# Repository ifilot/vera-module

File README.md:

# VERA Module Fork

This repository is a fork of the VERA module, the Video Embedded Retro Adapter
developed for the Commander X16 computer. It contains the PCB designs, FPGA
source, firmware, programmer utilities, documentation, and manufacturing support
files for the module.

This fork keeps the original project history available while adding forked PCB
variants that can be reviewed, rendered, and published independently from the
upstream Commander X16-branded board files.

## What Changed In This Fork

- Added `pcb/fork-r0/` as the first forked board variant.
- Added `pcb/fork-r1/` as the current forked board variant.
- Removed/reworked branding that should not be reused outside the Commander X16
  project.
- Migrated the fork boards to modern KiCad project files.
- Added local symbol/cache fixes for migrated KiCad schematics so parts render
  and connect as intended.
- Added Docker-based placement-site generation for `fork-r0` and `fork-r1`.
- Added a GitHub Pages workflow that can publish the generated placement site.

The older upstream board revisions remain under `pcb/rev0/` through `pcb/rev4/`
for reference.

## Repository Layout

- `pcb/fork-r0/`: first forked PCB variant.
- `pcb/fork-r1/`: current forked PCB variant.
- `pcb/rev*/`: original/upstream board revisions.
- `fpga/`: VERA FPGA source and project files.
- `programmer/stm32/`: STM32 firmware for the programmer.
- `programmer/programmer_tool/`: host-side programmer tool.
- `doc/`: VERA documentation and datasheets.
- `deploy/`: scripts and configuration for generated placement and manufacturing
  outputs.

## Placement Website

Generate the placement website locally with:

```sh
./deploy/generate-placement-site.sh
```

The default build intentionally renders only the two fork boards:

- `pcb/fork-r0/fork-r0.kicad_pcb`
- `pcb/fork-r1/fork-r1.kicad_pcb`

The generated output is written to:

- `deploy/site/index.html`
- `deploy/site/fork-r0/index.html`
- `deploy/site/fork-r0/placements.csv`
- `deploy/site/fork-r1/index.html`
- `deploy/site/fork-r1/placements.csv`

The script prefers the Docker image `ghcr.io/inti-cmnb/kicad10_auto:latest`,
which contains KiCad, KiBot, and InteractiveHtmlBom. If Docker is unavailable, it
falls back to local KiBot/InteractiveHtmlBom tools, and finally to a limited
built-in preview generator.

## Manufacturing Files

Generate the complete local manufacturing package with:

```sh
./deploy/generate-manufacturing-files.sh
```

This generates Gerbers, Excellon drill files, zipped Gerber upload packages, and
the JLCPCB BOM/CPL files for only the fork boards:

- `manufacturing/gerbers/fork-r0/`
- `manufacturing/gerbers/fork-r0.zip`
- `manufacturing/gerbers/fork-r1/`
- `manufacturing/gerbers/fork-r1.zip`
- `manufacturing/jlcpcb/fork-r0/`
- `manufacturing/jlcpcb/fork-r1/`

The Gerber export uses the Dockerized KiCad CLI from
`ghcr.io/inti-cmnb/kicad10_auto:latest` when Docker is available, and falls back
to a local `kicad-cli` installation otherwise.

## JLCPCB Assembly Files

Generate JLCPCB-style SMT assembly files with:

```sh
./deploy/generate-jlcpcb-files.sh
```

The generated files are written to:

- `manufacturing/jlcpcb/fork-r0/bom.csv`
- `manufacturing/jlcpcb/fork-r0/cpl.csv`
- `manufacturing/jlcpcb/fork-r0/missing_lcsc.csv`
- `manufacturing/jlcpcb/fork-r1/bom.csv`
- `manufacturing/jlcpcb/fork-r1/cpl.csv`
- `manufacturing/jlcpcb/fork-r1/missing_lcsc.csv`

The BOM contains `Comment`, `Designator`, `Footprint`, and `LCSC Part #`
columns. The CPL contains `Designator`, `Mid X`, `Mid Y`, `Layer`, and
`Rotation` columns. The exporter includes populated SMD footprints and skips
mounting holes, fiducials, logos, DNP parts, and footprints marked as excluded
from BOM or position files.

`missing_lcsc.csv` is a review file listing parts that still need a JLCPCB/LCSC
part number before automated assembly ordering.

You can also generate live JLCPCB part candidates:

```sh
ALLOW_JLCPCB_LOOKUP=1 ./deploy/find-jlcpcb-parts.sh
```

This sends BOM-derived search terms to `jlcpcb.com`, so it requires explicit
opt-in. It writes `bom_autofilled.csv` and `part_candidates.csv` beside each
board's BOM. The candidate finder prefers in-stock Basic/common parts and lower
prices, but the generated selections should still be reviewed before ordering.

## CI/CD

The GitHub Actions workflow in `.github/workflows/placement-site.yml` builds the
placement site for `fork-r0` and `fork-r1`. On `main` or `master`, it can publish
the generated `deploy/site/` output to GitHub Pages.

The workflow in `.github/workflows/manufacturing-files.yml` generates the same
manufacturing package as `./deploy/generate-manufacturing-files.sh` and uploads
it as a downloadable Actions artifact.

The workflows are triggered by changes to:

- `.github/workflows/placement-site.yml`
- `.github/workflows/manufacturing-files.yml`
- `deploy/**`
- `pcb/fork-r0/**`
- `pcb/fork-r1/**`

## Building Source Code

The STM32 programmer firmware can be built from `programmer/stm32/`:

```sh
make -C programmer/stm32
```

The host-side programmer tool lives in `programmer/programmer_tool/` and depends
on libusb development headers, for example `libusb-1.0-0-dev` on Debian/Ubuntu.

The FPGA source is under `fpga/`. The checked-in project targets the Lattice
iCE40UP5K device family and is intended to be built with the Lattice toolchain
used by the upstream VERA project.

## Branding Note

The Commander X16 logo belongs to the Commander X16 project. Do not reuse that
logo for unrelated boards, forks, or derivative projects unless you have explicit
permission.

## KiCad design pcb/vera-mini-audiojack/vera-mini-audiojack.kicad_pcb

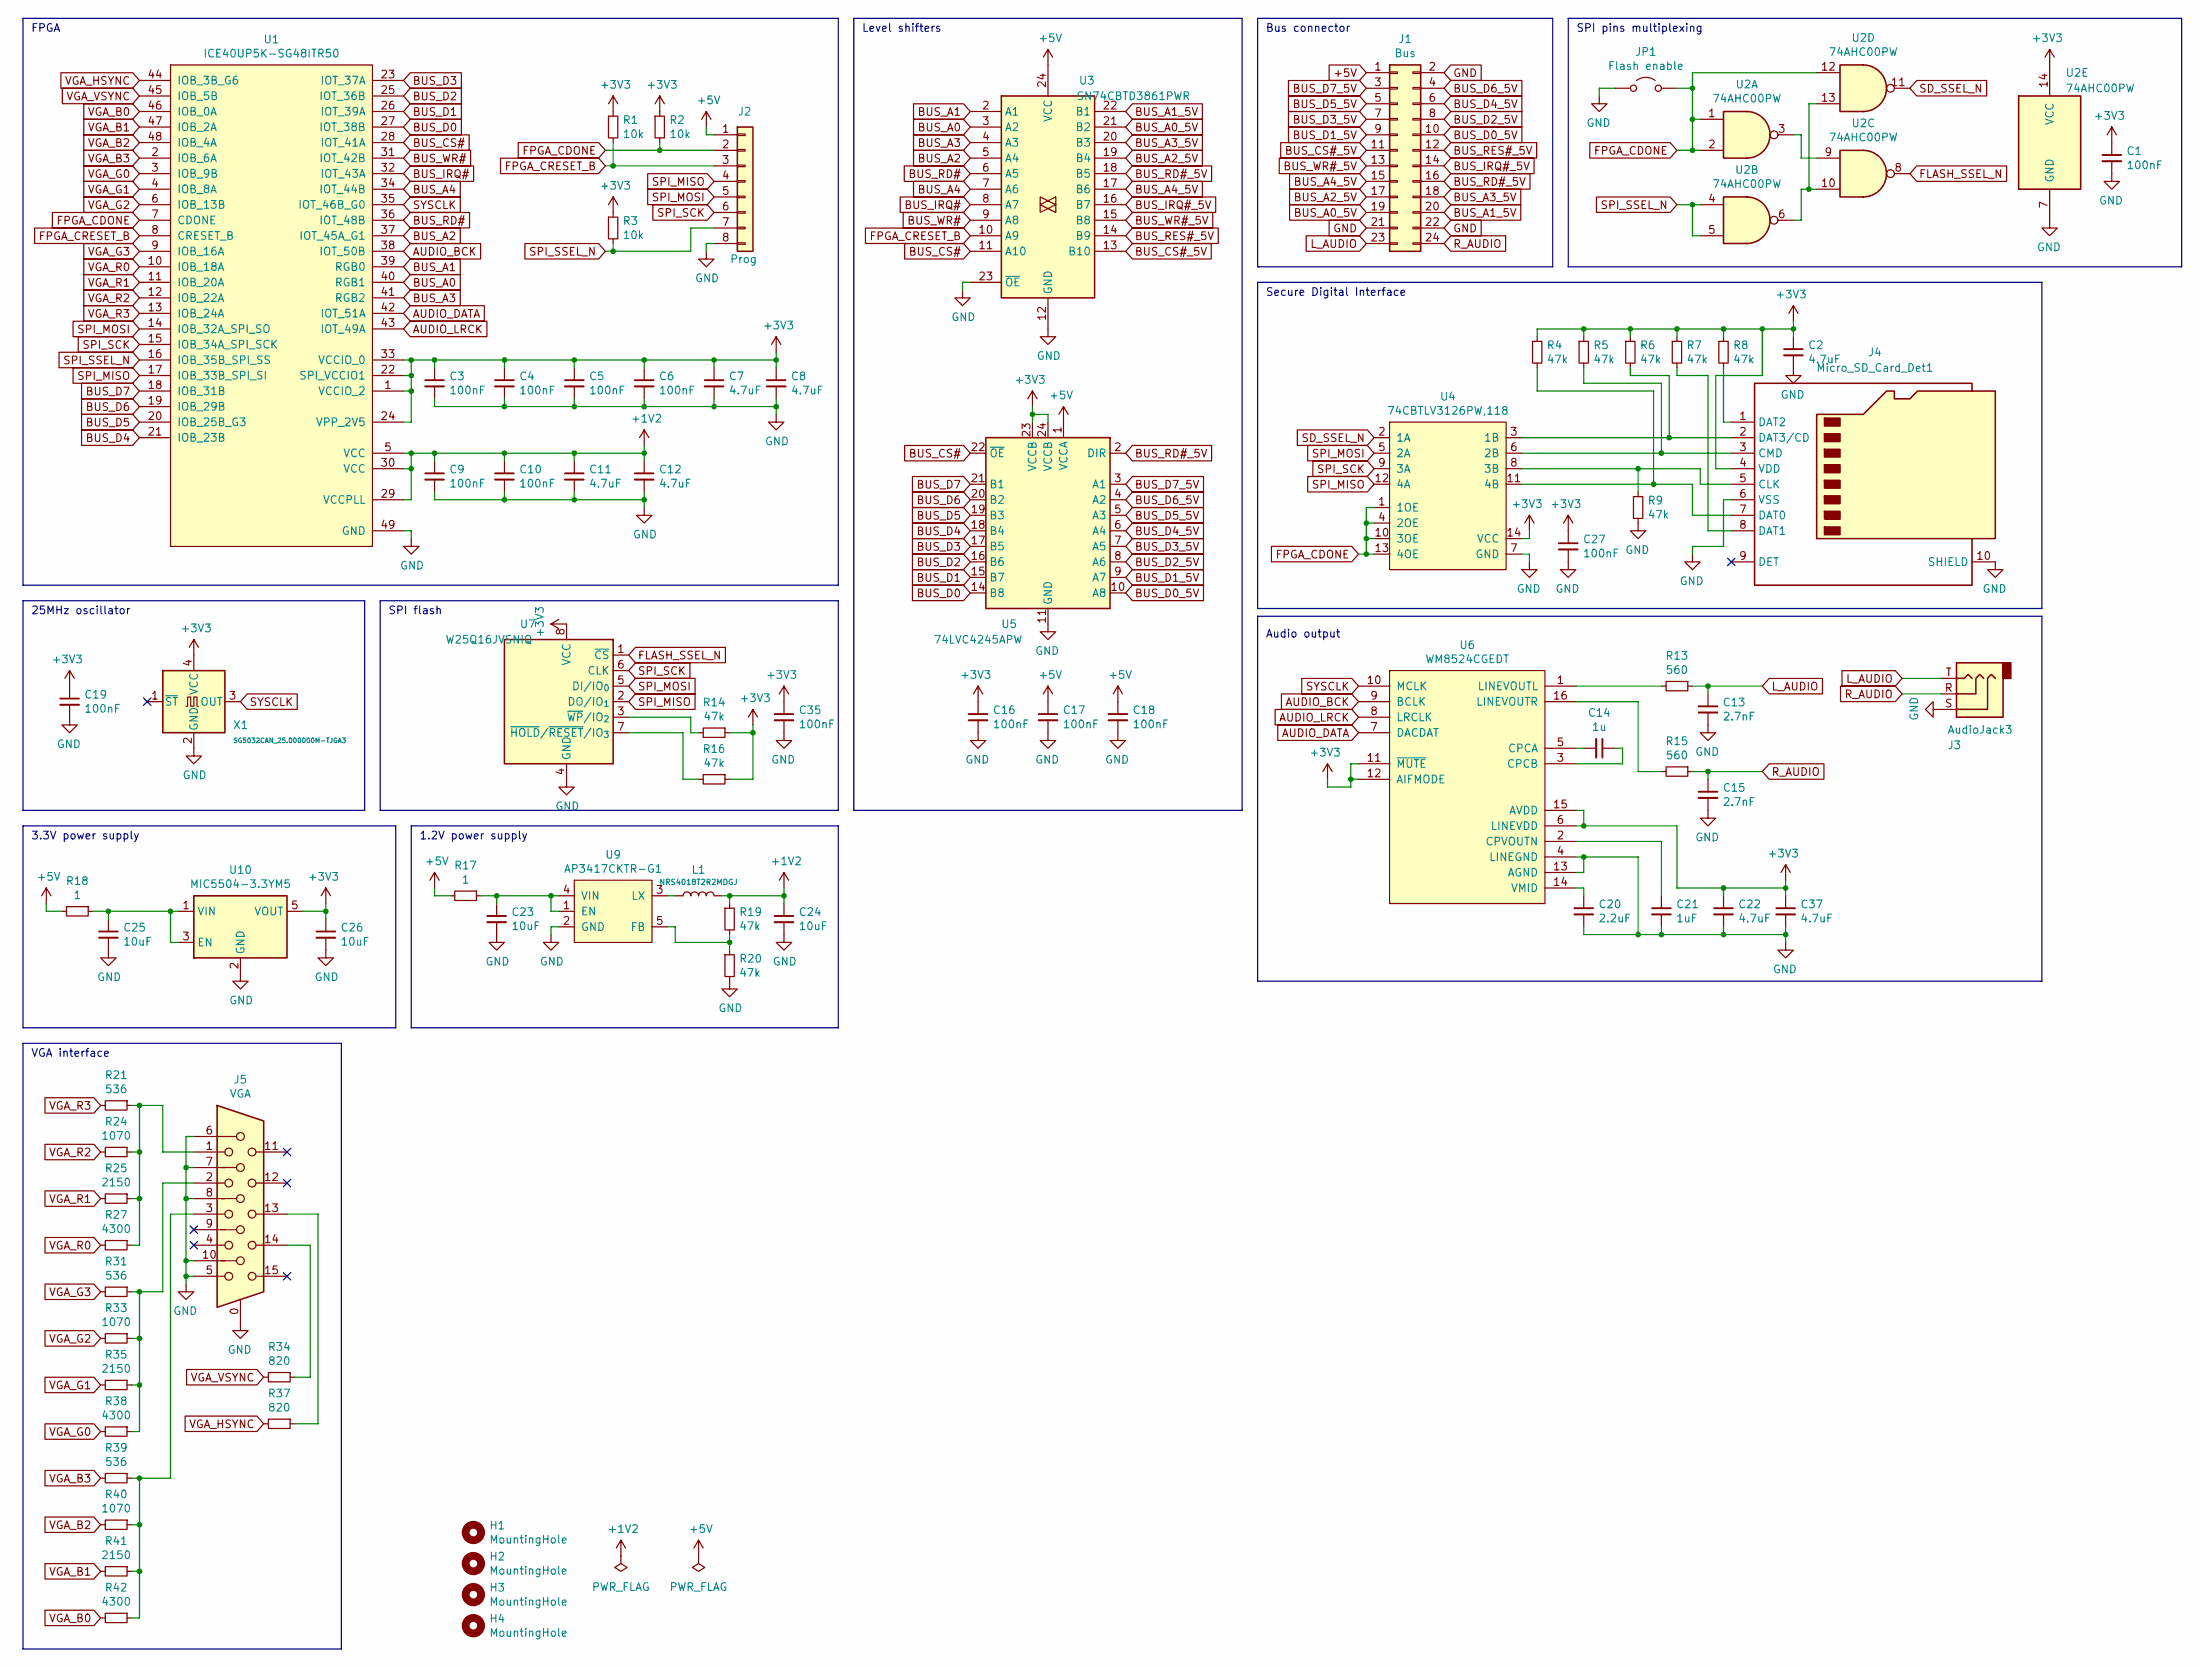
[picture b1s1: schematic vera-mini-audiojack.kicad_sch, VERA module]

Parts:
C1, C3, C4, C5, C6, C9, C10, C16, C17, C18, C19, C27, C35: 100nF; C_0603_1608Metric; LCSC Part # C14663
C2, C7, C8, C11, C12, C22, C37: 4.7uF; C_0603_1608Metric; LCSC Part # C19666
C13, C15: 2.7nF; C_0603_1608Metric
C14: 1u; C_0603_1608Metric
C20: 2.2uF; C_0603_1608Metric
C21: 1uF; C_0603_1608Metric
C23, C24, C25, C26: 10uF; C_0805_2012Metric; LCSC Part # C15850
H1, H2, H3, H4: MountingHole; MountingHole_3.2mm_M3_Pad_Via
J1: Bus; PinHeader_2x12_P2.54mm_Vertical
J2: Prog; PinHeader_1x08_P2.54mm_Vertical
J3: AudioJack3; Jack_3.5mm_CUI_SJ1-3525N_Horizontal
J4: Micro_SD_Card_Det1; CONN9_MSD-1_CUD; LCSC Part # C381082
J5: VGA; ICD15S13E4GV00LF
JP1: Flash enable; PinHeader_1x02_P2.54mm_Vertical
L1: NRS4018T2R2MDGJ; L_Bourns-SRN4018; LCSC Part # C92959
R1, R2, R3: 10k; R_0603_1608Metric; LCSC Part # C25804
R4, R5, R6, R7, R8, R9, R14, R16, R19, R20: 47k; R_0603_1608Metric; LCSC Part # C25819
R13, R15: 560; R_0603_1608Metric
R17, R18: 1; R_0603_1608Metric; LCSC Part # C22936
R21, R31, R39: 536; R_0603_1608Metric; LCSC Part # C17746
R24, R33, R40: 1070; R_0603_1608Metric; LCSC Part # C22762
R25, R35, R41: 2150; R_0603_1608Metric; LCSC Part # C22901
R27, R38, R42: 4300; R_0603_1608Metric; LCSC Part # C137712
R34, R37: 820; R_0603_1608Metric; LCSC Part # C23253
U1: ICE40UP5K-SG48ITR50; QFN-48-1EP_7x7mm_P0.5mm_EP5.3x5.3mm
U2: 74AHC00PW; TSSOP-14_4.4x5mm_P0.65mm; LCSC Part # C8143
U3: SN74CBTD3861PWR; TSSOP-24_4.4x7.8mm_P0.65mm
U4: 74CBTLV3126PW,118; TSSOP-14_4.4x5mm_P0.65mm
U5: 74LVC4245APW; TSSOP-24_4.4x7.8mm_P0.65mm; LCSC Part # C354456
U6: WM8524CGEDT; TSSOP-16_4.4x5mm_P0.65mm
U7: W25Q16JVSNIQ; SOIC-8_3.9x4.9mm_P1.27mm; LCSC Part # C2456211
U9: AP3417CKTR-G1; SOT-23-5
U10: MIC5504-3.3YM5; SOT-23-5; LCSC Part # C41348078
X1: SG5032CAN_25.000000M-TJGA3; Oscillator_SMD_SeikoEpson_SG8002LB-4Pin_5.0x3.2mm

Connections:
+1V2: C9.1, C10.1, C11.1, C12.1, C24.1, L1.2, R19.1, U1.5 (VCC), U1.29 (VCCPLL), U1.30 (VCC)
+3V3: C1.1, C2.1, C3.1, C4.1, C5.1, C6.1, C7.1, C8.1, C16.1, C19.1, C22.1, C26.1, C27.1, C35.1, C37.1, J4.4 (VDD), R1.1, R2.1, R3.1, R4.1, R5.1, R6.1, R7.1, R8.1, R14.1, R16.1, U1.1 (VCCIO_2), U1.22 (SPI_VCCIO1), U1.24 (VPP_2V5), U1.33 (VCCIO_0), U2.14 (VCC), U4.14 (VCC), U5.23 (VCCB), U5.24 (VCCB), U6.6 (LINEVDD), U6.11 (~MUTE), U6.12 (AIFMODE), U6.15 (AVDD), U7.8 (VCC), U10.5 (VOUT), X1.4 (VCC)
+5V: C17.1, C18.1, J1.1, J2.1, R17.2, R18.2, U3.24 (VCC), U5.1 (VCCA)
AUDIO_BCK: U1.38 (IOT_50B), U6.9 (BCLK)
AUDIO_DATA: U1.42 (IOT_51A), U6.7 (DACDAT)
AUDIO_LRCK: U1.43 (IOT_49A), U6.8 (LRCLK)
BUS_A0: U1.40 (RGB1), U3.3 (A2)
BUS_A0_5V: J1.19, U3.21 (B2)
BUS_A1: U1.39 (RGB0), U3.2 (A1)
BUS_A1_5V: J1.20, U3.22 (B1)
BUS_A2: U1.37 (IOT_45A_G1), U3.5 (A4)
BUS_A2_5V: J1.17, U3.19 (B4)
BUS_A3: U1.41 (RGB2), U3.4 (A3)
BUS_A3_5V: J1.18, U3.20 (B3)
BUS_A4: U1.34 (IOT_44B), U3.7 (A6)
BUS_A4_5V: J1.15, U3.17 (B6)
BUS_CS#: U1.28 (IOT_41A), U3.11 (A10), U5.22 (~OE)
BUS_CS#_5V: J1.11, U3.13 (B10)
BUS_D0: U1.27 (IOT_38B), U5.14 (B8)
BUS_D0_5V: J1.10, U5.10 (A8)
BUS_D1: U1.26 (IOT_39A), U5.15 (B7)
BUS_D1_5V: J1.9, U5.9 (A7)
BUS_D2: U1.25 (IOT_36B), U5.16 (B6)
BUS_D2_5V: J1.8, U5.8 (A6)
BUS_D3: U1.23 (IOT_37A), U5.17 (B5)
BUS_D3_5V: J1.7, U5.7 (A5)
BUS_D4: U1.21 (IOB_23B), U5.18 (B4)
BUS_D4_5V: J1.6, U5.6 (A4)
BUS_D5: U1.20 (IOB_25B_G3), U5.19 (B3)
BUS_D5_5V: J1.5, U5.5 (A3)
BUS_D6: U1.19 (IOB_29B), U5.20 (B2)
BUS_D6_5V: J1.4, U5.4 (A2)
BUS_D7: U1.18 (IOB_31B), U5.21 (B1)
BUS_D7_5V: J1.3, U5.3 (A1)
BUS_IRQ#: U1.32 (IOT_43A), U3.8 (A7)
BUS_IRQ#_5V: J1.14, U3.16 (B7)
BUS_RD#: U1.36 (IOT_48B), U3.6 (A5)
BUS_RD#_5V: J1.16, U3.18 (B5), U5.2 (DIR)
BUS_RES#_5V: J1.12, U3.14 (B9)
BUS_WR#: U1.31 (IOT_42B), U3.9 (A8)
BUS_WR#_5V: J1.13, U3.15 (B8)
FLASH_SSEL_N: U2.8, U7.1 (~CS)
FPGA_CDONE: J2.2, JP1.2 (B), R2.2, U1.7 (CDONE), U2.1, U2.2, U2.12, U4.1 (1OE), U4.4 (2OE), U4.10 (3OE), U4.13 (4OE)
FPGA_CRESET_B: J2.3, R1.2, U1.8 (CRESET_B), U3.10 (A9)
GND: C1.2, C2.2, C3.2, C4.2, C5.2, C6.2, C7.2, C8.2, C9.2, C10.2, C11.2, C12.2, C13.2, C15.2, C16.2, C17.2, C18.2, C19.2, C20.2, C21.2, C22.2, C23.2, C24.2, C25.2, C26.2, C27.2, C35.2, C37.2, J1.2, J1.21, J1.22, J2.8, J3.S, J4.6 (VSS), J4.10 (SHIELD), J5.0, J5.5, J5.6, J5.7, J5.8, J5.10, JP1.1 (A), R9.2, R20.2, U1.49 (GND), U2.7 (GND), U3.12 (GND), U3.23 (~OE), U4.7 (GND), U5.11 (GND), U5.12 (GND), U5.13 (GND), U6.4 (LINEGND), U6.13 (AGND), U7.4 (GND), U9.2 (GND), U10.2 (GND), X1.2 (GND)
L_AUDIO: C13.1, J1.23, J3.T, R13.1
unnamed: J4.5 (CLK), R9.1, U4.8 (3B)
unnamed: J4.3 (CMD), R5.2, U4.6 (2B)
unnamed: J4.7 (DAT0), R4.2, U4.11 (4B)
unnamed: J4.8 (DAT1), R7.2
unnamed: J4.1 (DAT2), R8.2
unnamed: J4.2 (DAT3/CD), R6.2, U4.3 (1B)
unnamed: J5.1, R21.1, R24.1, R25.1, R27.1
unnamed: J5.2, R31.1, R33.1, R35.1, R38.1
unnamed: J5.3, R39.1, R40.1, R41.1, R42.1
unnamed: J5.13, R37.1
unnamed: J5.14, R34.1
unnamed: U2.3, U2.9
unnamed: U2.6, U2.10, U2.13
unnamed: C14.2, U6.5 (CPCA)
unnamed: C14.1, U6.3 (CPCB)
unnamed: C21.1, U6.2 (CPVOUTN)
unnamed: R13.2, U6.1 (LINEVOUTL)
unnamed: R15.2, U6.16 (LINEVOUTR)
unnamed: C20.1, U6.14 (VMID)
unnamed: R16.2, U7.7 (~HOLD/~RESET/IO_{3})
unnamed: R14.2, U7.3 (~WP/IO_{2})
unnamed: C23.1, R17.1, U9.1 (EN), U9.4 (VIN)
unnamed: R19.2, R20.1, U9.5 (FB)
unnamed: L1.1, U9.3 (LX)
unnamed: C25.1, R18.1, U10.1 (VIN), U10.3 (EN)
R_AUDIO: C15.1, J1.24, J3.R, R15.1
SD_SSEL_N: U2.11, U4.2 (1A)
SPI_MISO: J2.4, U1.17 (IOB_33B_SPI_SI), U4.12 (4A), U7.2 (DO/IO_{1})
SPI_MOSI: J2.5, U1.14 (IOB_32A_SPI_SO), U4.5 (2A), U7.5 (DI/IO_{0})
SPI_SCK: J2.6, U1.15 (IOB_34A_SPI_SCK), U4.9 (3A), U7.6 (CLK)
SPI_SSEL_N: J2.7, R3.2, U1.16 (IOB_35B_SPI_SS), U2.4, U2.5
SYSCLK: U1.35 (IOT_46B_G0), U6.10 (MCLK), X1.3 (OUT)
VGA_B0: R42.2, U1.46 (IOB_0A)
VGA_B1: R41.2, U1.47 (IOB_2A)
VGA_B2: R40.2, U1.48 (IOB_4A)
VGA_B3: R39.2, U1.2 (IOB_6A)
VGA_G0: R38.2, U1.3 (IOB_9B)
VGA_G1: R35.2, U1.4 (IOB_8A)
VGA_G2: R33.2, U1.6 (IOB_13B)
VGA_G3: R31.2, U1.9 (IOB_16A)
VGA_HSYNC: R37.2, U1.44 (IOB_3B_G6)
VGA_R0: R27.2, U1.10 (IOB_18A)
VGA_R1: R25.2, U1.11 (IOB_20A)
VGA_R2: R24.2, U1.12 (IOB_22A)
VGA_R3: R21.2, U1.13 (IOB_24A)
VGA_VSYNC: R34.2, U1.45 (IOB_5B)

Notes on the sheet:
FPGA
Secure Digital Interface
Level shifters
3.3V power supply
SPI pins multiplexing
Bus connector
25MHz oscillator
Audio output
VGA interface
SPI flash
1.2V power supply

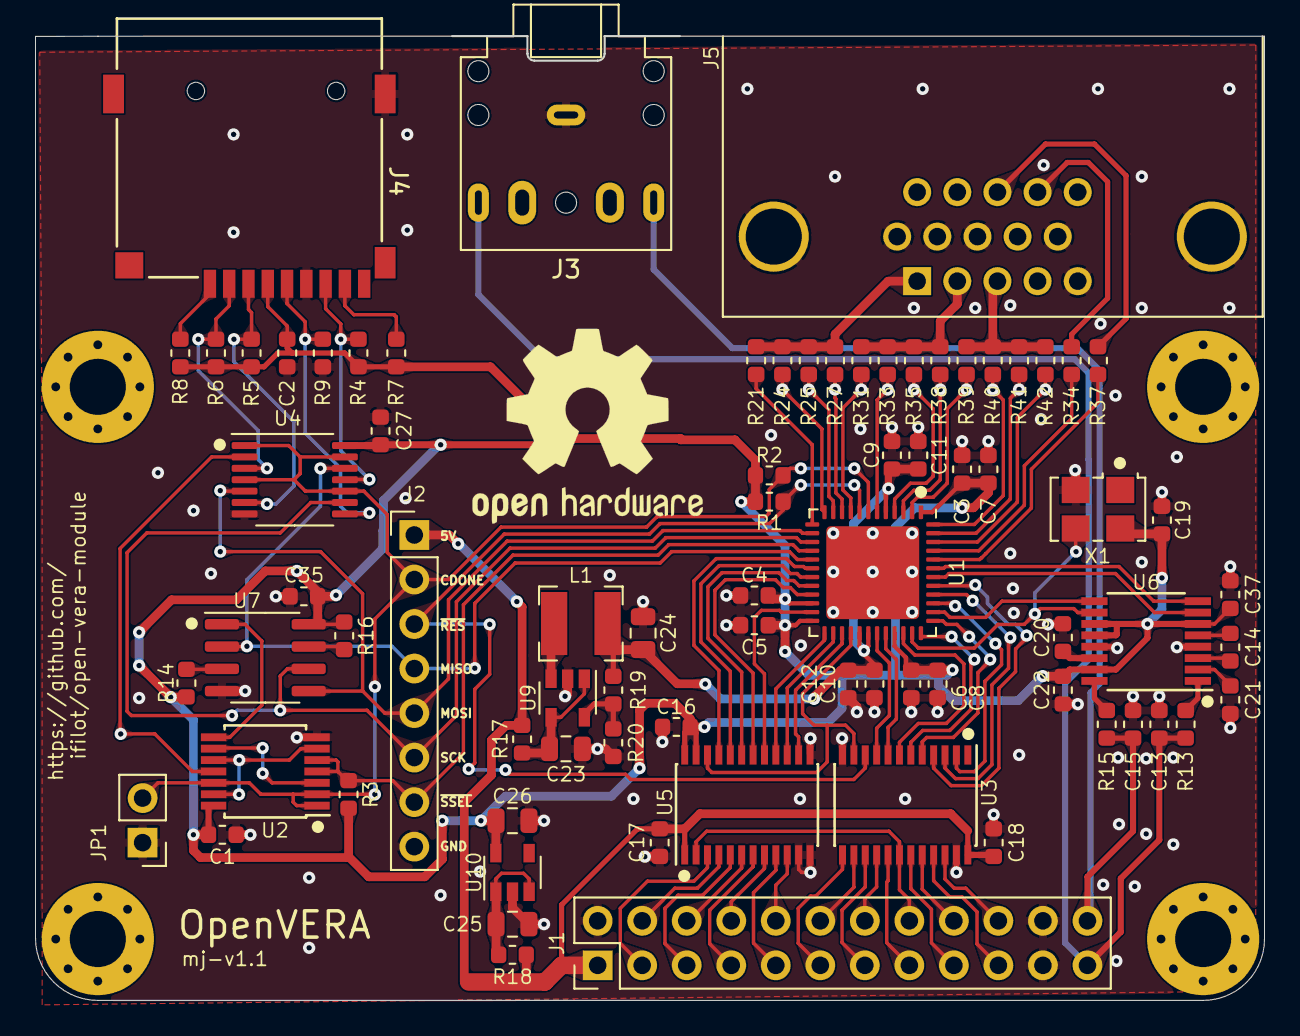
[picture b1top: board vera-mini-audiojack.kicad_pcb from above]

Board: 2 copper layers, 70.1 x 55.0 mm, 81 parts (0 on the bottom side), 92 nets.

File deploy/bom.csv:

Designator,Footprint,Quantity,Value,LCSC Part #
"C1, C10, C16, C17, C18, C19, C3, C35, C4, C5, C6, C9",0603,12,100nF,C14663
"C11, C12, C7, C8",0603,4,4.7uF,C19666
"C23, C24, C25, C26",0805,4,10uF,C15850
"D1, D2",0805,2,LED,C2296
"H1, H2, H3, H4",MountingHole_3.2mm_M3,4,MountingHole,
J1,PinHeader_2x12_P2.54mm_Vertical,1,Bus,
J2,PinHeader_1x08_P2.54mm_Vertical,1,Prog,
J5,ICD15S13E4GV00LF,1,VGA,
JP1,PinHeader_1x02_P2.54mm_Vertical,1,Flash enable,
L1,L_Bourns-SRN4018,1,NRS4018T2R2MDGJ,C92959
"R1, R2, R3, R4",0603,4,10k,C25804
"R14, R16, R19, R20",0603,4,47k,C25819
"R17, R18",0603,2,1,C22936
"R21, R31, R39",0603,3,536,C17746
"R24, R33, R40",0603,3,1070,C22762
"R25, R35, R41",0603,3,2150,C22901
"R27, R38, R42",0603,3,4300,C137712
"R34, R37",0603,2,820,C23253
"R5, R6",0603,2,68,C23228
SW1,SW_PUSH_6mm,1,SW_Push,
U1,QFN-48-1EP_7x7mm_P0.5mm_EP5.6x5.6mm,1,ICE40UP5K-SG48ITR,C2678152
U10,SOT-23-5,1,MIC5504-3.3YM5,C41348078
U2,TSSOP-14_4.4x5mm_P0.65mm,1,74AHC00PW,C8143
U3,TSSOP-24_4.4x7.8mm_P0.65mm,1,SN74CBTD3861PWR,C2655473
U5,TSSOP-24_4.4x7.8mm_P0.65mm,1,74LVC4245APW,C354456
U7,SOIC-8_3.9x4.9mm_P1.27mm,1,W25Q16JVSNIQ,C2456211
U9,SOT-23-5,1,AP3417CKTR-G1,C500759
X1,Oscillator_SMD_SeikoEpson_SG8002LB-4Pin_5.0x3.2mm,1,SG5032CAN_25.000000M-TJGA3,

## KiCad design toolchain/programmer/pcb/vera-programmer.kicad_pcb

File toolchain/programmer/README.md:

# VERA Raspberry Pi Pico programmer

This directory contains everything needed to build and use the VERA programmer:

- `firmware`: Raspberry Pi Pico firmware and its USB protocol
- `cli`: native Windows command-line flashing and verification tool
- `pcb`: KiCad schematic and PCB layout for the programmer hardware

See each subdirectory's README for build and usage instructions.

The PCB and firmware pin assignments are kept together in the firmware's
`programmer_config.h`. The board's dedicated READ (GPIO 26) and WRITE (GPIO 27)
LEDs show flash activity, while the Pico onboard LED (GPIO 25) shows whether the
FPGA completed booting.

The programmer firmware and CLI use the ecosystem version from the repository
root `VERSION` file.

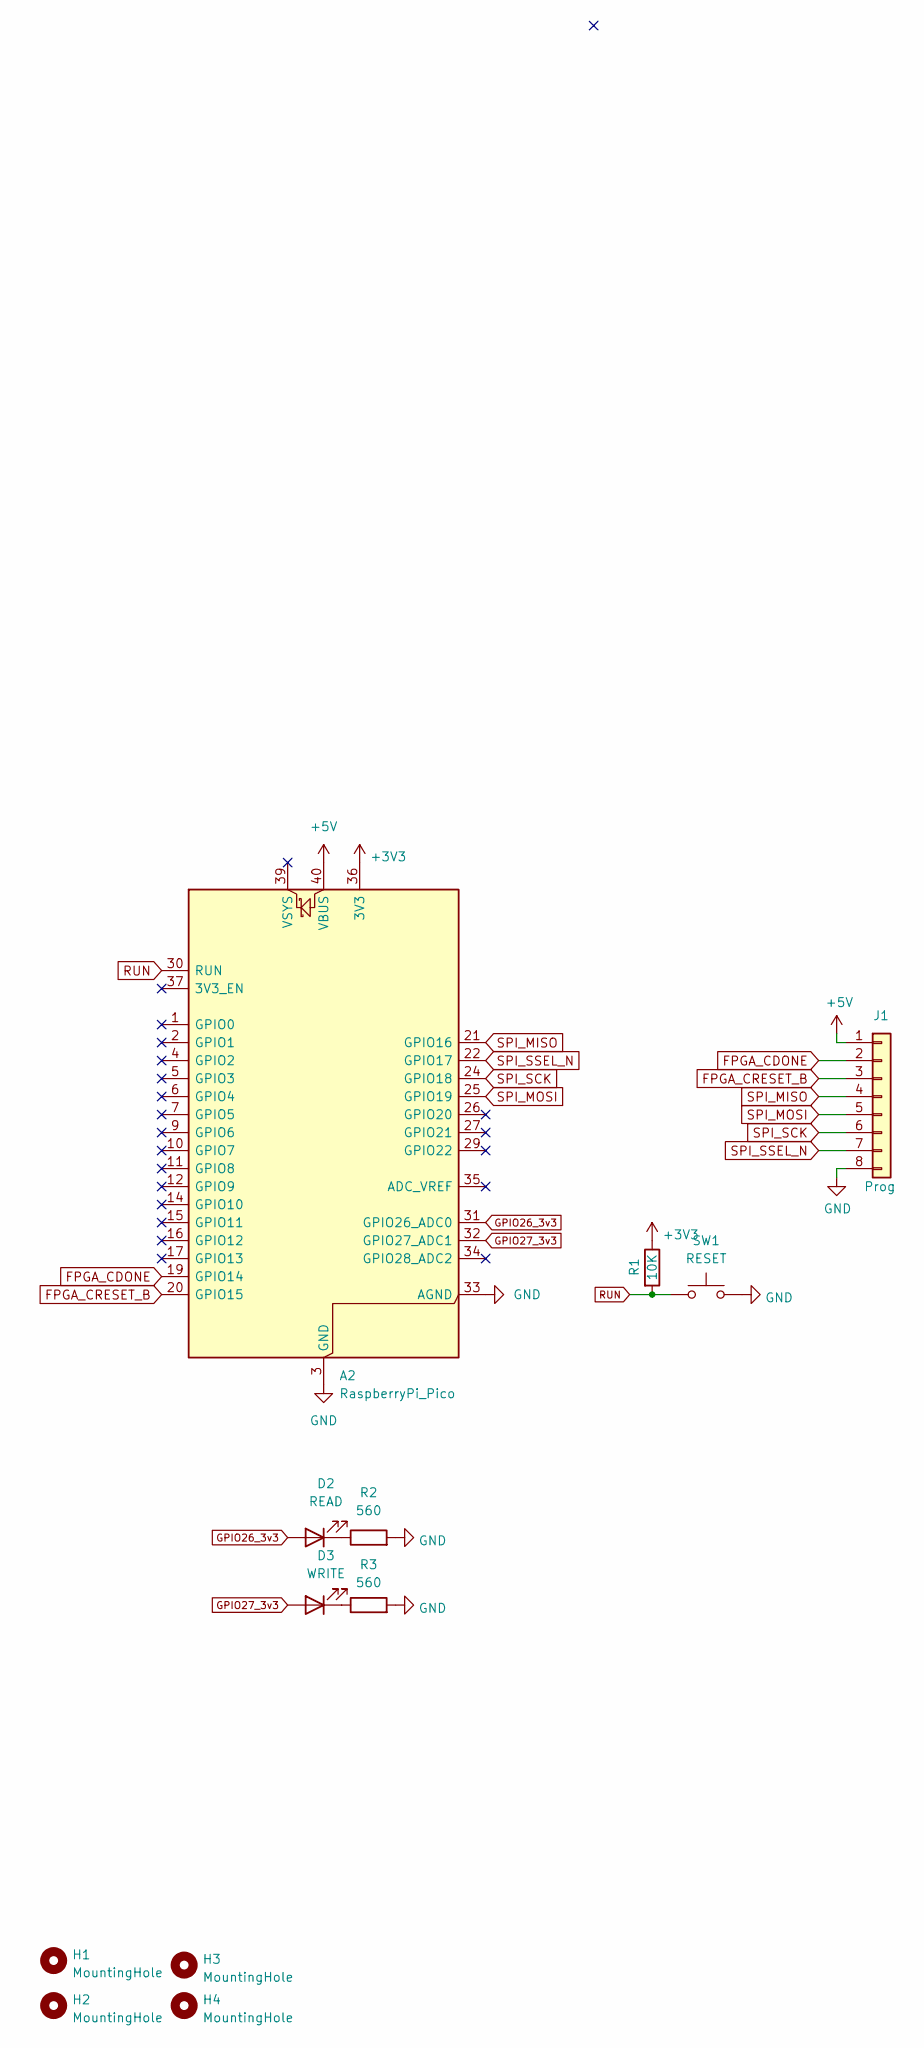
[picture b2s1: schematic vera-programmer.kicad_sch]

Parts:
A2: RaspberryPi_Pico; RaspberryPi_Pico_Common_Unspecified
D2: READ; LED_D5.0mm
D3: WRITE; LED_D5.0mm
H1, H2, H3, H4: MountingHole; MountingHole_3.2mm_M3
J1: Prog; PinHeader_1x08_P2.54mm_Vertical
R1: 10K; R_Axial_DIN0207_L6.3mm_D2.5mm_P7.62mm_Horizontal; LCSC C17414
R2, R3: 560; R_Axial_DIN0207_L6.3mm_D2.5mm_P7.62mm_Horizontal; LCSC C28636
SW1: RESET; SW_PUSH_6mm

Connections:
+3V3: A2.36 (3V3), R1.1
+5V: A2.40 (VBUS), J1.1
FPGA_CDONE: A2.19 (GPIO14), J1.2
FPGA_CRESET_B: A2.20 (GPIO15), J1.3
GND: A2.3 (GND), A2.8 (GND), A2.13 (GND), A2.18 (GND), A2.23 (GND), A2.28 (GND), A2.33 (AGND), A2.38 (GND), J1.8, R2.2, R3.2, SW1.2
GPIO26_3v3: A2.31 (GPIO26_ADC0), D2.2 (A)
GPIO27_3v3: A2.32 (GPIO27_ADC1), D3.2 (A)
unnamed: D2.1 (K), R2.1
unnamed: D3.1 (K), R3.1
RUN: A2.30 (RUN), R1.2, SW1.1
SPI_MISO: A2.21 (GPIO16), J1.4
SPI_MOSI: A2.25 (GPIO19), J1.5
SPI_SCK: A2.24 (GPIO18), J1.6
SPI_SSEL_N: A2.22 (GPIO17), J1.7

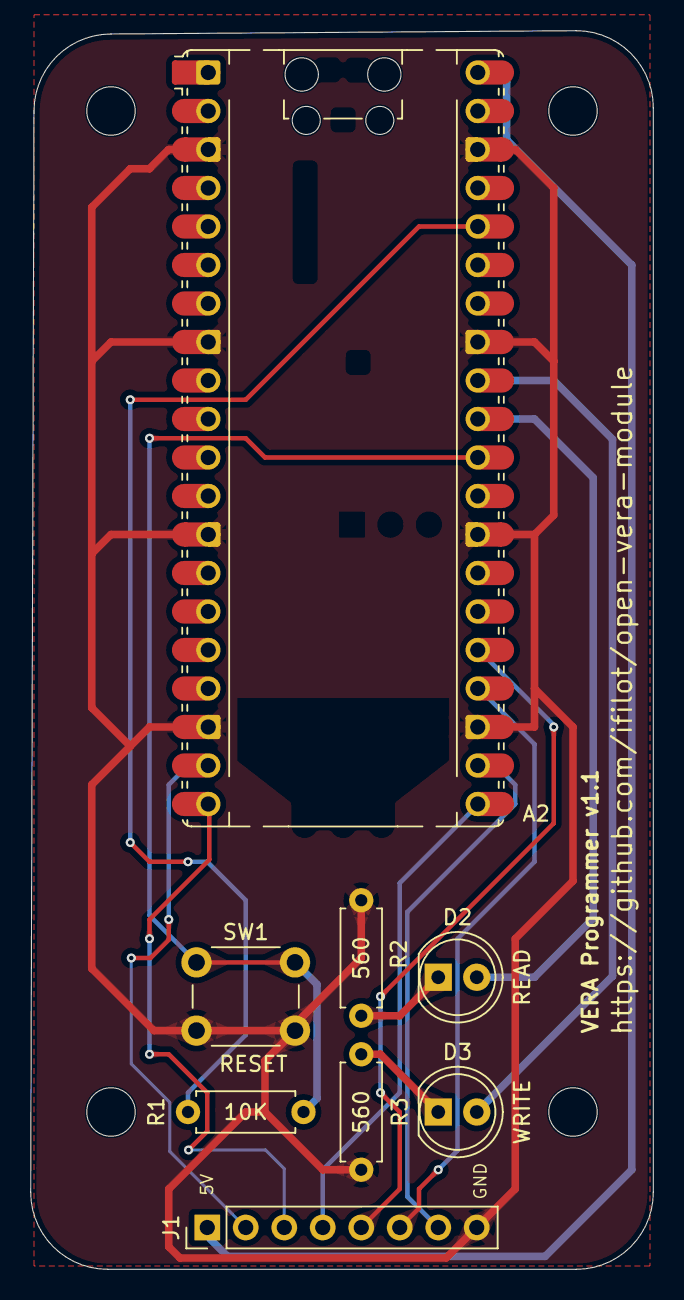
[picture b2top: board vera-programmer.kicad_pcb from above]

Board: 2 copper layers, 41.1 x 81.7 mm, 12 parts (0 on the bottom side), 14 nets.

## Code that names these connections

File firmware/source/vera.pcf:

# 25 MHz oscillator
set_io clk25 35
set_frequency clk25 25

# Host bus
set_io extbus_cs_n 28
set_io extbus_rd_n 36
set_io extbus_wr_n 31
set_frequency extbus_rd_n 8
set_frequency extbus_wr_n 8

set_io extbus_a[0] 40
set_io extbus_a[1] 39
set_io extbus_a[2] 37
set_io extbus_a[3] 41
set_io extbus_a[4] 34

set_io extbus_d[0] 27
set_io extbus_d[1] 26
set_io extbus_d[2] 25
set_io extbus_d[3] 23
set_io extbus_d[4] 21
set_io extbus_d[5] 20
set_io extbus_d[6] 19
set_io extbus_d[7] 18

set_io extbus_irq_n 32

# VGA
set_io vga_r[0] 10
set_io vga_r[1] 11
set_io vga_r[2] 12
set_io vga_r[3] 13
set_io vga_g[0] 3
set_io vga_g[1] 4
set_io vga_g[2] 6
set_io vga_g[3] 9
set_io vga_b[0] 46
set_io vga_b[1] 47
set_io vga_b[2] 48
set_io vga_b[3] 2
set_io vga_hsync 44
set_io vga_vsync 45

# SD-card SPI
set_io spi_sck 15
set_io spi_mosi 14
set_io spi_miso 17
set_io spi_ssel_n_sd 16

# Audio DAC
set_io audio_lrck 43
set_io audio_bck 38
set_io audio_data 42

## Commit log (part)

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2026-05-29 Creating forks
2026-05-29 Patching generation
2026-05-29 Adding component IDs
2026-05-29 Patching deployment
2026-05-29 Fix Pages deployment branch
2026-05-29 Creating manufacture files
2026-06-11 Improving R1

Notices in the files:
pcb/vera-mini-audiojack/vera-mini-audiojack.kicad_sch:
Original design by (C) 2020 Frank van den Hoef
